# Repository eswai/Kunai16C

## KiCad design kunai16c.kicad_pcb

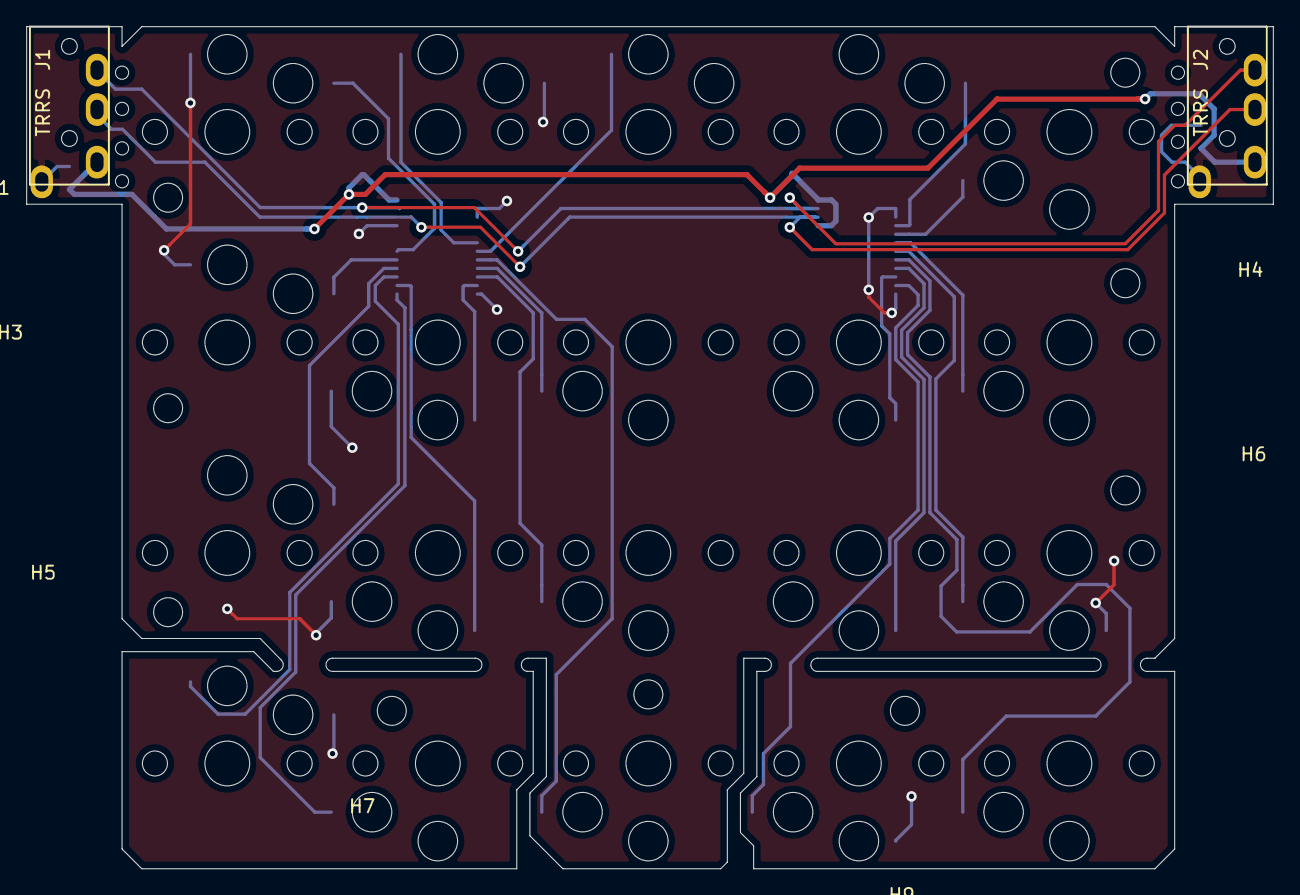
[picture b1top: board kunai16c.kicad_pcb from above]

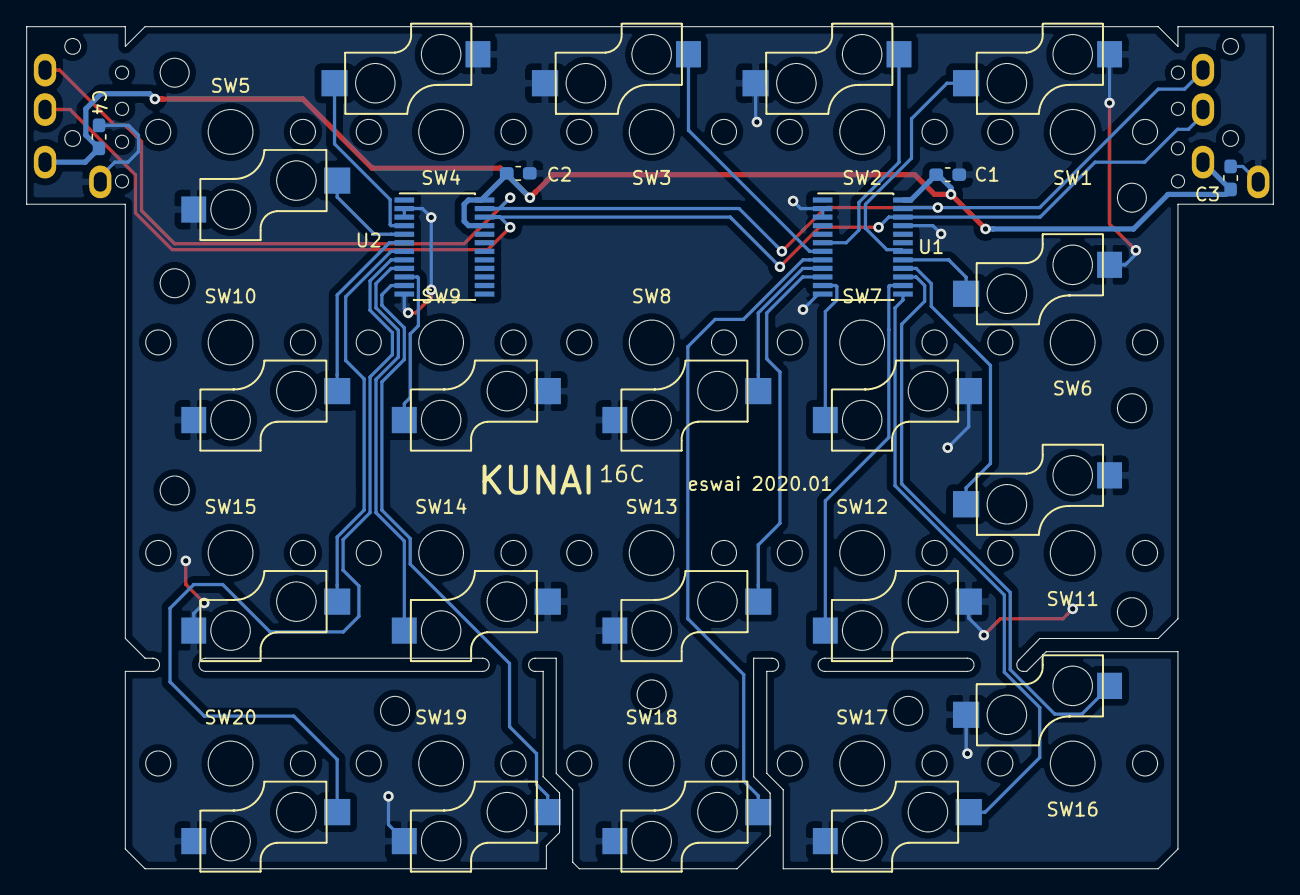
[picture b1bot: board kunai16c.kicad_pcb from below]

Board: 2 copper layers, 94.8 x 64.0 mm, 45 parts (6 on the bottom side), 24 nets.

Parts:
C1, C2: 100nF; C_0603_1608Metric_Pad1.05x0.95mm_HandSolder
C3, C4: 1uF; C_0603_1608Metric_Pad1.05x0.95mm_HandSolder
H1, H2, H3, H4, H5, H6, H7, H8, H9: MountingHole; MountingHole_2.2mm_M2
J1, J2: AudioJack4; MJ-4PP-9_v3
Ref**: Val**; HOLE_copy
Ref**#2, Ref**#3, Ref**#4, Ref**#5, Ref**#6, Ref**#7, Ref**#8: Val**; HOLE_copy
SW1, SW2, SW3, SW4, SW5, SW6, SW7, SW8, SW9, SW10, SW11, SW12, SW13, SW14, SW15, SW16, SW17, SW18, SW19, SW20: SW_PUSH; Choc_Hotswap
U1, U2: PCA9555PW; TSSOP-24_4.4x7.8mm_P0.65mm

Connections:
GND: C1.2, C2.2, C3.2, C4.2, J1.S, J2.S, SW1.2, SW2.1, SW3.1, SW4.2, SW5.2, SW6.2, SW7.1, SW8.2, SW9.1, SW10.2, SW11.2, SW12.1, SW13.2, SW14.1, SW15.2, SW16.1, SW17.2, SW18.2, SW19.2, SW20.2, U1.2, U1.3, U1.12, U1.21, U2.2, U2.3, U2.12
S1: SW1.1, U1.18
S2: SW2.2, U1.6
S3: SW3.2, U1.7
S4: SW4.1, U2.4
S5: SW5.1, U2.5
S6: SW6.1, U1.17
S7: SW7.2, U1.11
S8: SW8.1, U1.9
S9: SW9.2, U2.10
S10: SW10.1, U2.6
S11: SW11.1, U1.16
S12: SW12.2, U1.14
S13: SW13.1, U1.10
S14: SW14.2, U2.9
S15: SW15.1, U2.7
S16: SW16.2, U1.15
S17: SW17.1, U1.13
S18: SW18.1, U1.8
S19: SW19.1, U2.11
S20: SW20.1, U2.8
SCL: J1.R1, J2.R1, U1.22, U2.22
SDA: J1.R2, J2.R2, U1.23, U2.23
VCC: C1.1, C2.1, C3.1, C4.1, J1.T, J2.T, U1.24, U2.21, U2.24

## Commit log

2020-01-05 GND問題の修正版
